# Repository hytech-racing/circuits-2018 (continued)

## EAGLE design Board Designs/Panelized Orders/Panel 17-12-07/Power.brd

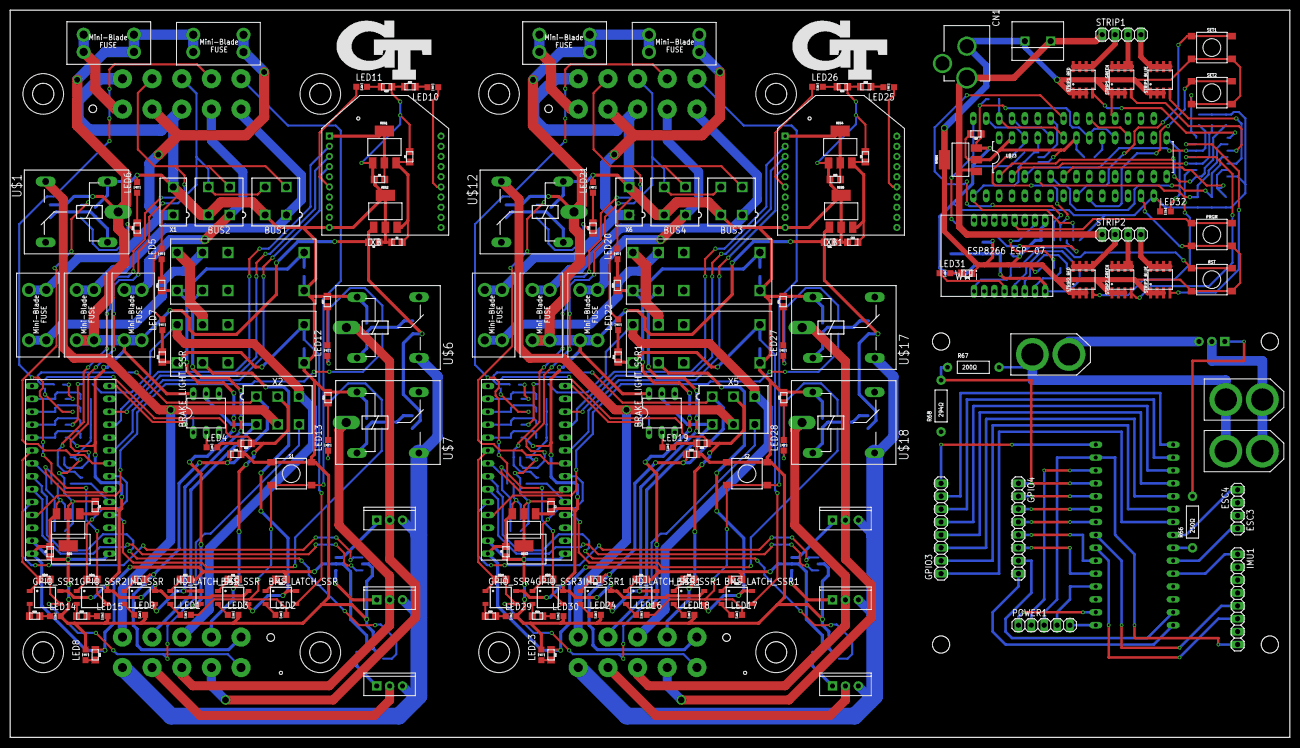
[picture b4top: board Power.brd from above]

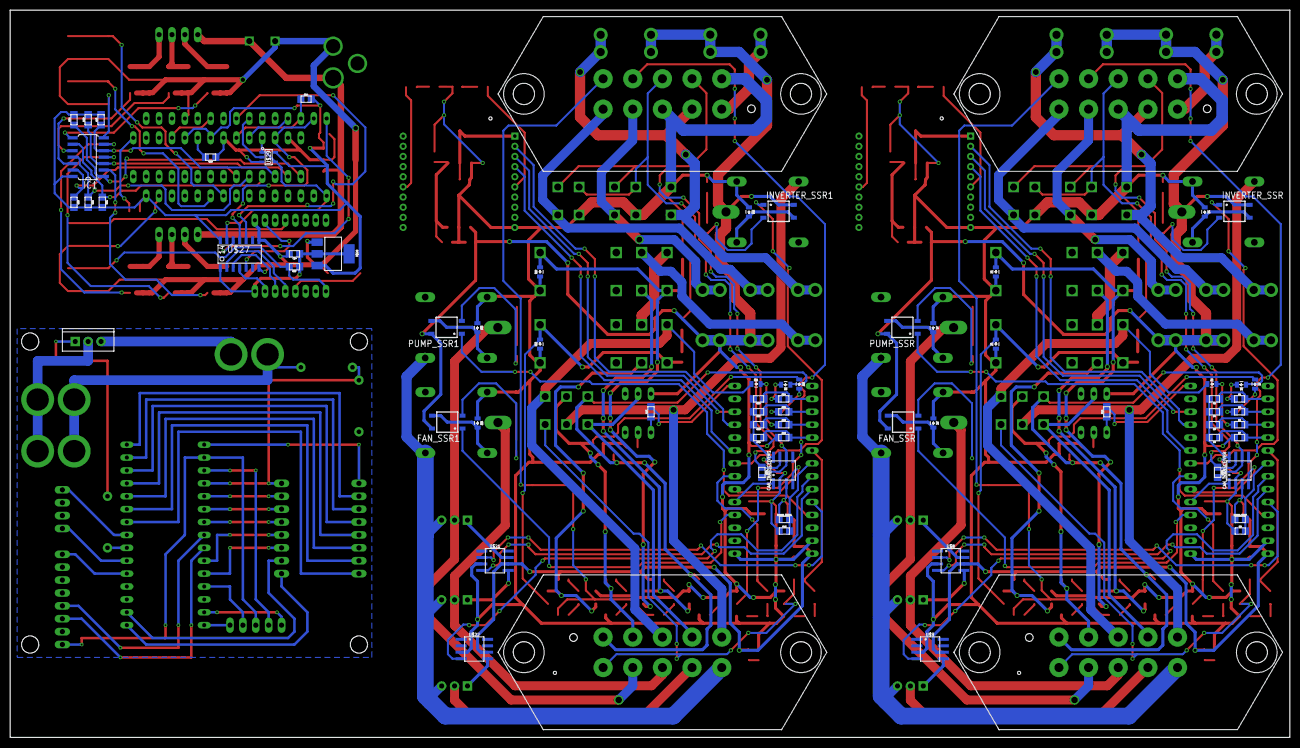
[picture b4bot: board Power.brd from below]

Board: 2 copper layers, 252.1 x 143.3 mm, 244 parts (71 on the bottom side), 240 nets.

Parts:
5VREG: SOT223
BATTERY_POWER1: XT60
BMS_LATCH_SSR, BMS_LATCH_SSR1: CPC1002N; SOP04
BMS_SSR, BMS_SSR1: CPC1002N; SOP04
BOARD_TEMP, BOARD_TEMP1: THERMISTOR_NCP210805; 0805
BRAKE_LIGHT_SSR, BRAKE_LIGHT_SSR1: SOLID_STATE_RELAY_VO14642AT; DIL06
BUS1, BUS2, BUS3, BUS4: CONNECTOR-4; MINIFIT_5566-4
C1, C5, C7, C11: .22uF; 0805
C2, C6, C8, C12: .1uF; 0805
C3, C4, C9, C10: 1uF; 0805
C13: .1µF; 0805
C14: 1µF; 0805
CAN_TRANSCEIVER, CAN_TRANSCEIVER1: MCP2551; SOIC-08
CN1: DCJACK_2MM_PTH
D1, D2, D3, D4, D5, D6, D7, D8, D9, D10, D11, D12, D13, D14, D15, D16: DIODE0805; 0805_D
ESC1_POWER1, ESC2_POWER1: XT60
ESC3, ESC4: M02; 1X02
FAN_SSR, FAN_SSR1: CPC1002N; SOP04
FH_FUSE, FH_FUSE1: 8A; MINI-BLADE_FUSE_HOLDER
FSAE_FUSE, FSAE_FUSE1: 8A; MINI-BLADE_FUSE_HOLDER
FUSE_BUS_1, FUSE_BUS_2, FUSE_BUS_3, FUSE_BUS_4: 5A; MINI-BLADE_FUSE_HOLDER
GPIO3, GPIO4: 1X08
GPIO_SSR1, GPIO_SSR2, GPIO_SSR3, GPIO_SSR4: CPC1002N; SOP04
IC1: 74HC04D; SO14
IMD_LATCH_SSR, IMD_LATCH_SSR1: CPC1002N; SOP04
IMD_SHUTDOWN, IMD_SHUTDOWN1, IMD_SHUTDOWN2, IMD_SHUTDOWN3: G2RL-2-DC12; G2RL-2
IMD_SSR, IMD_SSR1: CPC1002N; SOP04
IMU1: 1X08
INVERTER_SSR, INVERTER_SSR1: CPC1002N; SOP04
LED1, LED2, LED16, LED17: White; LED-805
LED3, LED7, LED11, LED18, LED22, LED26: Green; LED-805
LED4, LED6, LED10, LED12, LED13, LED14, LED15, LED19, LED21, LED25, LED27, LED28, LED29, LED30, LED31: Red; LED-805
LED5, LED9, LED20, LED24: Yellow; LED-805
LED8, LED23: Purple; LED-805
LED32: LED-805
POWER1: 1X05
POWER_MOSFET1: TO-220-SINK
PRGM: TACTILE_SWITCH_SMD_6.2MM_TALL
PUMP_SSR, PUMP_SSR1: CPC1002N; SOP04
R1, R3, R5, R7, R24, R36, R38, R40: 43k; 0805
R2, R4, R6, R8, R35, R37, R39, R41: 12k; 0805
R9, R19, R42, R45, R56, R57, R58, R59, R60, R61, R62, R63: 10k; 0805
R10, R11, R16, R25, R26, R29, R30, R43, R53, R54: 43; 0805
R12, R13, R23, R27, R28, R31, R32, R50, R51, R52: 33; 0805
R14, R17, R21, R33, R44, R48: 820; 0805
R15, R34: 120; 0805
R18, R46, R55: 2.2k; 0805
R20, R47: 270; 0805
R22, R49, R64: 100; 0805
R66: 250Ω; AXIAL-0.4
R67: 200Ω; AXIAL-0.4
R68: 294Ω; AXIAL-0.4
REG, REG2, REG3, REG5: 5V; SOT223
REG1, REG4: TLV1117LV33; SOT223
RST: TACTILE_SWITCH_SMD_6.2MM_TALL
S1, S2: TACTILE_SWITCH_SMD_6.2MM_TALL
SET1, SET2: TACTILE_SWITCH_SMD_6.2MM_TALL
SHUTDWN_FUSE, SHUTDWN_FUSE1: 5A; MINI-BLADE_FUSE_HOLDER
STRIP1, STRIP2: 1X04
STRIP1_BLUE, STRIP1_GREEN, STRIP1_RED, STRIP2_BLUE, STRIP2_GREEN, STRIP2_RED: MDS1656; SOIC-08
U$1, U$6, U$7, U$12, U$17, U$18: G5LE; ZF112
U$2, U$4, U$5, U$14, U$15, U$16: N-CHANNEL_MOSFETGENERIC; TO-220-SINK
U$3, U$13: TEENSY_3.2_SIMPLE
U$8, U$9, U$21, U$22: MC34152; SOIC-08
U$10, U$11, U$19, U$20: JUMPER; 0805
U$23: TLC5940; DIL28-3
U$24, U$31: ARDUINO_NANO
U$25: TERMINAL_BLOCK_DG301-02P; DG301-02P
U$26: ESP8266_ESP-07
U$27: SOIC-14
U$28: TLV1117LV33; SOT223
U$29: SN74LVC1G08; SOT-23-5
X1, X6: CONNECTOR-2; MINIFIT_5566-2
X2, X5: CONNECTOR-6; MINIFIT_5566-6
X3, X4, X7, X8: CONNECTOR-10MX150L_VERTICAL-10; MX150L_VERTICAL-10
XB, XB1: XBEE

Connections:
3.3V1: IMU1.8, POWER1.3, U$31.3.3V
5V1: POWER1.4, U$31.5V
12VSUPPLY_BRB: FH_FUSE.R1, FH_FUSE.R2, SHUTDWN_FUSE.R1, SHUTDWN_FUSE.R2, X1.1, X4.2
12VSUPPLY_BRB1: FH_FUSE1.R1, FH_FUSE1.R2, SHUTDWN_FUSE1.R1, SHUTDWN_FUSE1.R2, X6.1, X8.2
12VSUPPLY_FSAE: FSAE_FUSE.R1, FSAE_FUSE.R2, X4.1
12VSUPPLY_FSAE1: FSAE_FUSE1.R1, FSAE_FUSE1.R2, X8.1
12VSUPPLY_READ: R7.2, R8.1, U$3.A3
12VSUPPLY_READ1: R40.2, R41.1, U$13.A3
12V_F1: BUS1.1, FUSE_BUS_1.R1, FUSE_BUS_1.R2, X4.5
12V_F2: BUS2.1, FUSE_BUS_2.R1, FUSE_BUS_2.R2, X4.4
12V_F3: BUS3.1, FUSE_BUS_3.R1, FUSE_BUS_3.R2, X8.5
12V_F4: BUS4.1, FUSE_BUS_4.R1, FUSE_BUS_4.R2, X8.4
+3V3: C14.1, R57.1, U$26.P$8, U$27.1, U$28.2, U$28.4
+5V: BOARD_TEMP.1, C2.2, CAN_TRANSCEIVER.3, R12.2, R13.1, R20.1, REG.3, U$3.VIN, U$8.6, U$9.6
+5V1: BOARD_TEMP1.1, C8.2, CAN_TRANSCEIVER1.3, R31.2, R32.1, R47.1, REG3.3, U$13.VIN, U$21.6, U$22.6
+5V2: 5VREG.3, C13.1, IC1.14, LED32.A, R56.2, R58.2, R59.2, R60.2, R61.2, R62.2, R63.2, U$23.19, U$23.21, U$24.VIN, U$27.14, U$28.3, U$29.5
+12V: BMS_SSR.4, BRAKE_LIGHT_SSR.6, C1.2, C5.2, FAN_SSR.4, FH_FUSE.L1, FH_FUSE.L2, FSAE_FUSE.L1, FSAE_FUSE.L2, FUSE_BUS_1.L1, FUSE_BUS_1.L2, FUSE_BUS_2.L1, FUSE_BUS_2.L2, GPIO_SSR1.4, GPIO_SSR2.4, IMD_SSR.4, INVERTER_SSR.4, PUMP_SSR.4, R7.1, REG.1, REG2.1, U$1.P
+12V1: BMS_SSR1.4, BRAKE_LIGHT_SSR1.6, C7.2, C11.2, FAN_SSR1.4, FH_FUSE1.L1, FH_FUSE1.L2, FSAE_FUSE1.L1, FSAE_FUSE1.L2, FUSE_BUS_3.L1, FUSE_BUS_3.L2, FUSE_BUS_4.L1, FUSE_BUS_4.L2, GPIO_SSR3.4, GPIO_SSR4.4, IMD_SSR1.4, INVERTER_SSR1.4, PUMP_SSR1.4, R40.1, REG3.1, REG5.1, U$12.P
+12V2: 5VREG.1, CN1.PWR, STRIP1.1, STRIP2.1, U$25.1
A4: GPIO4.1, R67.P$1, R68.P$2, U$31.A0
A5: GPIO4.2, U$31.A1
A8: GPIO4.3, U$31.A2
A9: GPIO4.4, U$31.A3
A10: GPIO4.5, U$31.A6
A11: GPIO4.6, U$31.A7
AREF1: POWER1.2, U$31.AREF
BLANK: R56.1, U$23.23, U$24.D10
BMS_COIL_PWR: BMS_LATCH_SSR.3, D5.C, IMD_SHUTDOWN1.4, IMD_SHUTDOWN1.COIL-, R17.1
BMS_COIL_PWR1: BMS_LATCH_SSR1.3, D13.C, IMD_SHUTDOWN3.4, IMD_SHUTDOWN3.COIL-, R44.1
BMS_OK: D2.A, R11.2, R19.1, X2.2, X3.2
BMS_OK1: D10.A, R26.2, R45.1, X5.2, X7.2
BMS_OK_READ: R3.2, R4.1, U$3.A1
BMS_OK_READ1: R36.2, R37.1, U$13.A1
BMS_PWR_STEP: BMS_LATCH_SSR.4, BMS_SSR.3, IMD_SHUTDOWN1.3
BMS_PWR_STEP1: BMS_LATCH_SSR1.4, BMS_SSR1.3, IMD_SHUTDOWN3.3
BRAKE_LIGHT: BRAKE_LIGHT_SSR.5, X2.4, X3.4
BRAKE_LIGHT1: BRAKE_LIGHT_SSR1.5, X5.4, X7.4
BRAKE_LIGHT_CTRL: R10.2, U$3.D12
BRAKE_LIGHT_CTRL1: R25.2, U$13.D12
CANH: BUS1.4, BUS2.4, CAN_TRANSCEIVER.7, R15.1, X4.8
CANH1: BUS3.4, BUS4.4, CAN_TRANSCEIVER1.7, R34.1, X8.8
CANL: BUS1.3, BUS2.3, CAN_TRANSCEIVER.6, R15.2, X4.7
CANL1: BUS3.3, BUS4.3, CAN_TRANSCEIVER1.6, R34.2, X8.7
D0(RX)1: GPIO4.7, U$31.D0(RX)
D1: GPIO3.8, U$31.D13
D1(TX)1: GPIO4.8, U$31.D1(TX)
D2: GPIO3.7, U$31.D12
D3: GPIO3.6, U$31.D11
D4: GPIO3.5, U$31.D10
D5: GPIO3.4, U$31.D9
D14: GPIO3.3, U$31.D8
D15: GPIO3.2, U$31.D7
D16: GPIO3.1, U$31.D6
DRIVE1: R66.P$1, U$31.D4
ESC3: ESC3.2, U$31.D3
ESC4: ESC4.2, U$31.D5
FAN1-: U$4.2, U$7.P, X3.8
FAN1-1: U$15.2, U$18.P, X7.8
FAN2-: U$5.2, X3.9
FAN2-1: U$16.2, X7.9
GND: BUS1.2, BUS2.2, C1.1, C2.1, C3.2, C4.1, C5.1, C6.1, CAN_TRANSCEIVER.2, CAN_TRANSCEIVER.8, D4.A, D5.A, D6.A, D7.A, D8.A, IMD_SHUTDOWN.COIL+, IMD_SHUTDOWN1.COIL+, LED3.C, LED4.C, LED5.C, LED6.C, LED7.C, LED8.C, LED9.C, LED14.C, LED15.C, R2.2, R4.2, R6.2, R8.2, R9.1, R18.2, R19.2, R22.1, R23.1, R27.2, R28.2, REG.2, REG.4, REG1.1, REG2.2, REG2.4, S1.B1, S1.B2, U$1.2, U$3.AGND, U$3.GND, U$6.1, U$7.1, U$8.3, U$9.3, X1.2, X4.3, X4.6, XB.10
GND1: U$2.3, U$4.3, U$5.3, U$6.S, U$7.S, X3.10
GND2: BUS3.2, BUS4.2, C7.1, C8.1, C9.2, C10.1, C11.1, C12.1, CAN_TRANSCEIVER1.2, CAN_TRANSCEIVER1.8, D12.A, D13.A, D14.A, D15.A, D16.A, IMD_SHUTDOWN2.COIL+, IMD_SHUTDOWN3.COIL+, LED18.C, LED19.C, LED20.C, LED21.C, LED22.C, LED23.C, LED24.C, LED29.C, LED30.C, R35.2, R37.2, R39.2, R41.2, R42.1, R45.2, R46.2, R49.1, R50.1, R51.2, R52.2, REG3.2, REG3.4, REG4.1, REG5.2, REG5.4, S2.B1, S2.B2, U$12.2, U$13.AGND, U$13.GND, U$17.1, U$18.1, U$21.3, U$22.3, X6.2, X8.3, X8.6, XB1.10
GND3: U$14.3, U$15.3, U$16.3, U$17.S, U$18.S, X7.10
GND4: 5VREG.2, 5VREG.4, C13.2, C14.2, CN1.GND, IC1.7, PRGM.A1, PRGM.A2, R55.1, R64.1, RST.A1, RST.A2, SET1.A1, SET1.A2, SET2.A1, SET2.A2, STRIP1_BLUE.1, STRIP1_BLUE.2, STRIP1_BLUE.3, STRIP1_GREEN.1, STRIP1_GREEN.2, STRIP1_GREEN.3, STRIP1_RED.1, STRIP1_RED.2, STRIP1_RED.3, STRIP2_BLUE.1, STRIP2_BLUE.2, STRIP2_BLUE.3, STRIP2_GREEN.1, STRIP2_GREEN.2, STRIP2_GREEN.3, STRIP2_RED.1, STRIP2_RED.2, STRIP2_RED.3, U$23.22, U$23.27, U$24.GND, U$24.GND1, U$25.2, U$26.P$9, U$27.7, U$27.8, U$28.1, U$29.3
GND6: BATTERY_POWER1.-, ESC3.1, ESC4.1, IMU1.7, POWER1.1, POWER_MOSFET1.3, R68.P$1, U$31.GND, U$31.GND1
GPIO_1: GPIO_SSR1.3, U$10.2, X2.6, X3.6
GPIO_2: GPIO_SSR2.3, U$11.2, X4.9
GPIO_3: GPIO_SSR3.3, U$20.2, X8.9
GPIO_4: GPIO_SSR4.3, U$19.2, X5.6, X7.6
GPIO_CTRL1: GPIO_SSR1.1, U$3.A4, U$10.1
GPIO_CTRL2: GPIO_SSR2.1, U$3.D5, U$11.1
GPIO_CTRL4: GPIO_SSR3.1, U$13.D5, U$20.1
GPIO_CTRL6: GPIO_SSR4.1, U$13.A4, U$19.1
IMD_COIL_PWR: D6.C, IMD_LATCH_SSR.3, IMD_SHUTDOWN.4, IMD_SHUTDOWN.COIL-, R14.1
IMD_COIL_PWR1: D14.C, IMD_LATCH_SSR1.3, IMD_SHUTDOWN2.4, IMD_SHUTDOWN2.COIL-, R33.1
IMD_PWR_STEP: IMD_LATCH_SSR.4, IMD_SHUTDOWN.3, IMD_SSR.3
IMD_PWR_STEP1: IMD_LATCH_SSR1.4, IMD_SHUTDOWN2.3, IMD_SSR1.3
INT1: IMU1.1, U$31.D2
INVERTER_CTRL: INVERTER_SSR.1, U$3.D6
INVERTER_CTRL1: INVERTER_SSR1.1, U$13.D6
INVERTER_SUPPLY: U$1.S, X2.5, X3.5
INVERTER_SUPPLY1: U$12.S, X5.5, X7.5
LATCH_EXT_BUTTON: LED1.C, LED2.C, S1.A1, S1.A2, X4.10
LATCH_EXT_BUTTON1: LED16.C, LED17.C, S2.A1, S2.A2, X8.10
MISO: U$24.D12, U$27.12
MISO_33: U$26.P$6, U$27.3
MOSI: U$23.26, U$24.D11, U$27.11
MOSI_33: U$26.P$7, U$27.4
unnamed: IMD_LATCH_SSR.2, LED1.A
unnamed: CAN_TRANSCEIVER.4, U$3.D4(CANRX)
unnamed: CAN_TRANSCEIVER.1, U$3.D3(CANTX)
unnamed: D7.C, PUMP_SSR.3, U$6.2
unnamed: IMD_LATCH_SSR.1, R12.1
unnamed: GPIO_SSR1.2, R29.1
unnamed: BRAKE_LIGHT_SSR.2, LED4.A
unnamed: GPIO_SSR2.2, R30.1
unnamed: BMS_SSR.2, LED3.A
unnamed: LED10.A, XB.15
unnamed: LED10.C, R22.2
unnamed: BMS_LATCH_SSR.1, R13.2
unnamed: LED14.A, R29.2
unnamed: LED15.A, R30.2
unnamed: BOARD_TEMP.2, R9.2, U$3.A5
unnamed: BMS_LATCH_SSR.2, LED2.A
unnamed: BRAKE_LIGHT_SSR.1, R10.1
unnamed: BMS_SSR.1, R11.1
unnamed: LED5.A, R14.2
unnamed: D8.C, FAN_SSR.3, U$7.2
unnamed: CAN_TRANSCEIVER1.4, U$13.D4(CANRX)
unnamed: D1.C, R1.1
unnamed: D2.C, R3.1
unnamed: D3.C, R5.1
unnamed: LED11.A, XB.6
unnamed: D4.C, INVERTER_SSR.3, U$1.1
unnamed: INVERTER_SSR.2, R16.1
unnamed: LED6.A, R16.2
unnamed: LED8.A, R20.2
unnamed: CAN_TRANSCEIVER1.1, U$13.D3(CANTX)
unnamed: IMD_SSR.1, R21.2
unnamed: LED7.A, R17.2
unnamed: LED11.C, R23.2
unnamed: IMD_SSR.2, LED9.A
unnamed: C3.1, C6.2, REG1.3, REG2.3
unnamed: LED13.C, R28.1
unnamed: LED12.C, R27.1
unnamed: LED12.A, PUMP_SSR.2
unnamed: U$2.1, U$8.7
unnamed: U$4.1, U$8.5
unnamed: U$5.1, U$9.5
unnamed: FAN_SSR.2, LED13.A
unnamed: BOARD_TEMP1.2, R42.2, U$13.A5
unnamed: IMD_LATCH_SSR1.2, LED16.A
unnamed: BMS_SSR1.2, LED18.A
unnamed: BMS_SSR1.1, R26.1
unnamed: BRAKE_LIGHT_SSR1.2, LED19.A
unnamed: BRAKE_LIGHT_SSR1.1, R25.1
unnamed: LED20.A, R33.2
unnamed: D9.C, R24.1
unnamed: D10.C, R36.1
unnamed: D11.C, R38.1
unnamed: D12.C, INVERTER_SSR1.3, U$12.1
unnamed: INVERTER_SSR1.2, R43.1
unnamed: LED21.A, R43.2
unnamed: IMD_LATCH_SSR1.1, R31.1
unnamed: BMS_LATCH_SSR1.2, LED17.A
unnamed: BMS_LATCH_SSR1.1, R32.2
unnamed: LED22.A, R44.2
unnamed: LED23.A, R47.2
unnamed: IMD_SSR1.2, LED24.A
unnamed: IMD_SSR1.1, R48.2
unnamed: LED25.A, XB1.15
unnamed: LED25.C, R49.2
unnamed: LED26.C, R50.2
unnamed: LED26.A, XB1.6
unnamed: C9.1, C12.2, REG4.3, REG5.3
unnamed: U$14.1, U$21.7
unnamed: U$15.1, U$21.5
unnamed: U$16.1, U$22.5
unnamed: D15.C, PUMP_SSR1.3, U$17.2
unnamed: D16.C, FAN_SSR1.3, U$18.2
unnamed: LED28.C, R52.1
unnamed: LED27.C, R51.1
unnamed: LED27.A, PUMP_SSR1.2
unnamed: FAN_SSR1.2, LED28.A
unnamed: GPIO_SSR4.2, R53.1
unnamed: GPIO_SSR3.2, R54.1
unnamed: LED29.A, R53.2
unnamed: LED30.A, R54.2
unnamed: R55.2, U$23.20
unnamed: U$23.18, U$24.D3
unnamed: STRIP2.2, STRIP2_RED.5, STRIP2_RED.6, STRIP2_RED.7, STRIP2_RED.8
unnamed: STRIP1.2, STRIP1_RED.5, STRIP1_RED.6, STRIP1_RED.7, STRIP1_RED.8
unnamed: STRIP1.3, STRIP1_GREEN.5, STRIP1_GREEN.6, STRIP1_GREEN.7, STRIP1_GREEN.8
unnamed: STRIP1.4, STRIP1_BLUE.5, STRIP1_BLUE.6, STRIP1_BLUE.7, STRIP1_BLUE.8
unnamed: STRIP2.3, STRIP2_GREEN.5, STRIP2_GREEN.6, STRIP2_GREEN.7, STRIP2_GREEN.8
unnamed: STRIP2.4, STRIP2_BLUE.5, STRIP2_BLUE.6, STRIP2_BLUE.7, STRIP2_BLUE.8
unnamed: R57.2, RST.B1, RST.B2, U$26.P$1
unnamed: IC1.2, STRIP2_RED.4
unnamed: IC1.4, STRIP2_GREEN.4
unnamed: IC1.8, STRIP1_RED.4
unnamed: IC1.10, STRIP1_GREEN.4
unnamed: IC1.12, STRIP1_BLUE.4
unnamed: IC1.6, STRIP2_BLUE.4
unnamed: IC1.1, R58.1, U$23.1
unnamed: IC1.3, R59.1, U$23.2
unnamed: IC1.5, R60.1, U$23.3
unnamed: IC1.13, R63.1, U$23.6
unnamed: IC1.11, R62.1, U$23.5
unnamed: IC1.9, R61.1, U$23.4
unnamed: PRGM.B1, PRGM.B2, U$26.P$12
unnamed: LED31.A, U$26.P$4
unnamed: LED32.C, U$23.15
unnamed: LED31.C, R64.2
unnamed: POWER_MOSFET1.1, R66.P$2
OKHS: D1.A, R18.1, R21.1, X2.1, X3.1
OKHS1: D9.A, R46.1, R48.1, X5.1, X7.1
OKHS_READ: R1.2, R2.1, U$3.A0
OKHS_READ1: R24.2, R35.1, U$13.A0
PUMP1-: U$2.2, U$6.P, X3.7
PUMP1-1: U$14.2, U$17.P, X7.7
PWM_CTRL1: U$3.A8, U$8.2
PWM_CTRL2: U$3.A7, U$8.4
PWM_CTRL3: U$3.A6, U$9.4
PWM_CTRL4: U$13.A6, U$22.4
PWM_CTRL5: U$13.A7, U$21.4
PWM_CTRL6: U$13.A8, U$21.2
RELAY_CTRL1: PUMP_SSR.1, U$3.A9
RELAY_CTRL2: FAN_SSR.1, U$3.D2
RELAY_CTRL3: FAN_SSR1.1, U$13.D2
RELAY_CTRL4: PUMP_SSR1.1, U$13.A9
SCK: U$23.25, U$24.D13, U$27.13, U$29.1, U$29.4
SCK_33: U$26.P$5, U$27.2
SCL1: IMU1.6, U$31.A5
SDA1: IMU1.5, U$31.A4
SET1: SET1.B1, SET1.B2, U$24.A5
SET2: SET2.B1, SET2.B2, U$24.A6
SHUTDOWN_A: IMD_SHUTDOWN.6, SHUTDWN_FUSE.L1, SHUTDWN_FUSE.L2
SHUTDOWN_A1: IMD_SHUTDOWN2.6, SHUTDWN_FUSE1.L1, SHUTDWN_FUSE1.L2
SHUTDOWN_B: IMD_SHUTDOWN.5, IMD_SHUTDOWN1.6
SHUTDOWN_B1: IMD_SHUTDOWN2.5, IMD_SHUTDOWN3.6
SHUTDOWN_C: D3.A, IMD_SHUTDOWN1.5, X2.3, X3.3
SHUTDOWN_C1: D11.A, IMD_SHUTDOWN3.5, X5.3, X7.3
SHUTDOWN_OUT_READ: R5.2, R6.1, U$3.A2
SHUTDOWN_OUT_READ1: R38.2, R39.1, U$13.A2
SS_ESP8266: U$24.D5, U$27.10
SS_ESP8266_33: U$26.P$10, U$27.5
SS_TLC5940: U$24.D6, U$29.2
SUPPLY+1: BATTERY_POWER1.+, ESC1_POWER1.+, ESC2_POWER1.+, R67.P$2
SUPPLY-1: ESC1_POWER1.-, ESC2_POWER1.-, POWER_MOSFET1.2
VCC: C4.2, REG1.2, REG1.4, XB.1
VCC1: C10.2, REG4.2, REG4.4, XB1.1
VIN1: POWER1.5, U$31.VIN
XB1: U$13.D7(RX3), XB1.4
XB8: U$3.D7(RX3), XB.4
XBDI: U$3.D10(TX2), XB.3
XBDI1: U$13.D10(TX2), XB1.3
XBDO: U$3.D9(RX2), XB.2
XBDO1: U$13.D9(RX2), XB1.2
XLAT: U$23.24, U$24.D9

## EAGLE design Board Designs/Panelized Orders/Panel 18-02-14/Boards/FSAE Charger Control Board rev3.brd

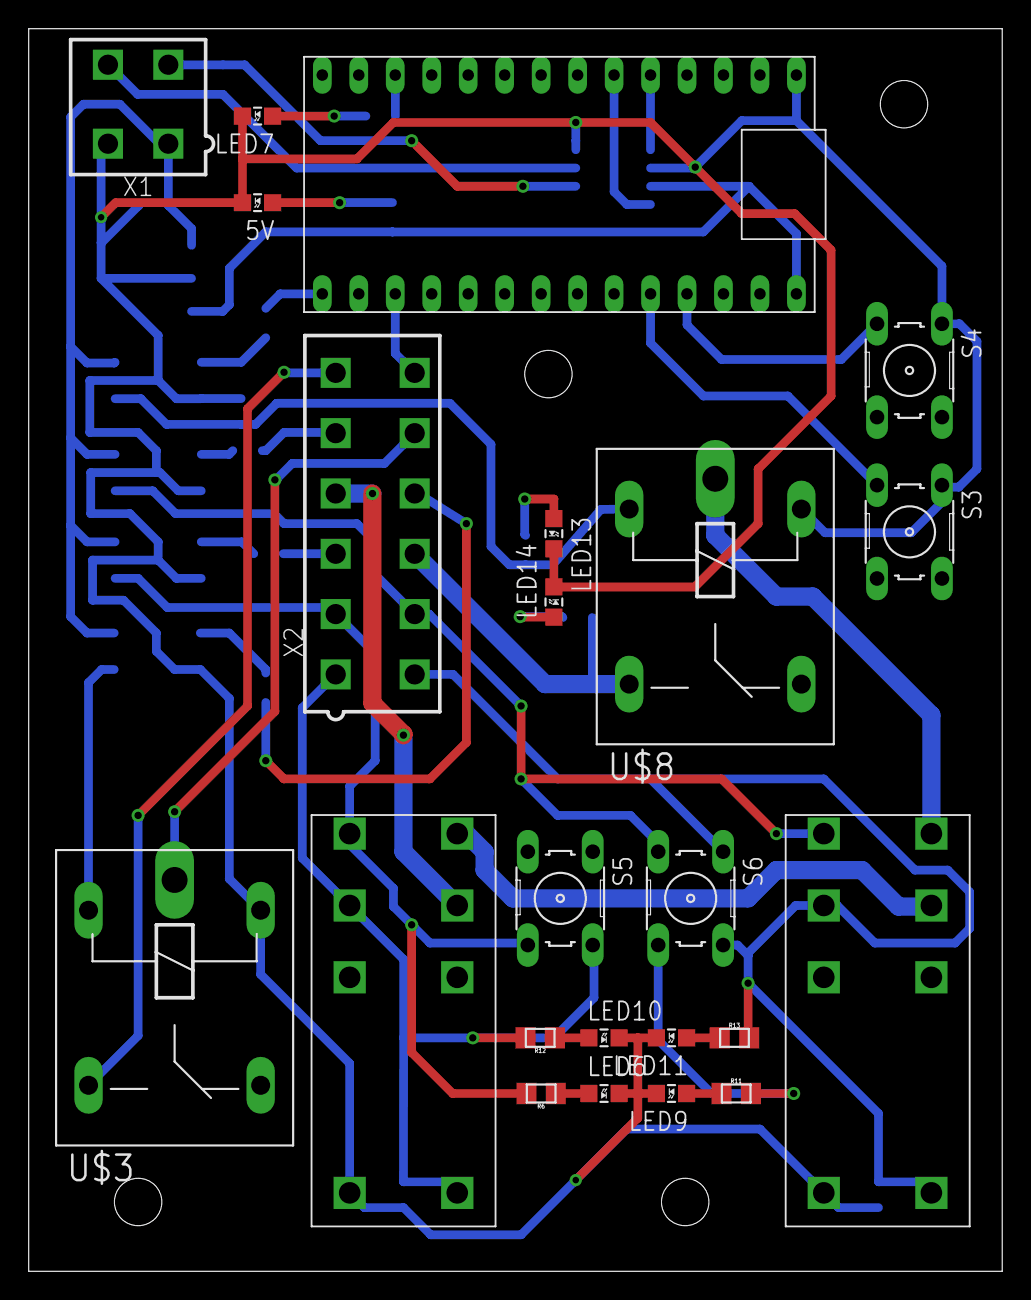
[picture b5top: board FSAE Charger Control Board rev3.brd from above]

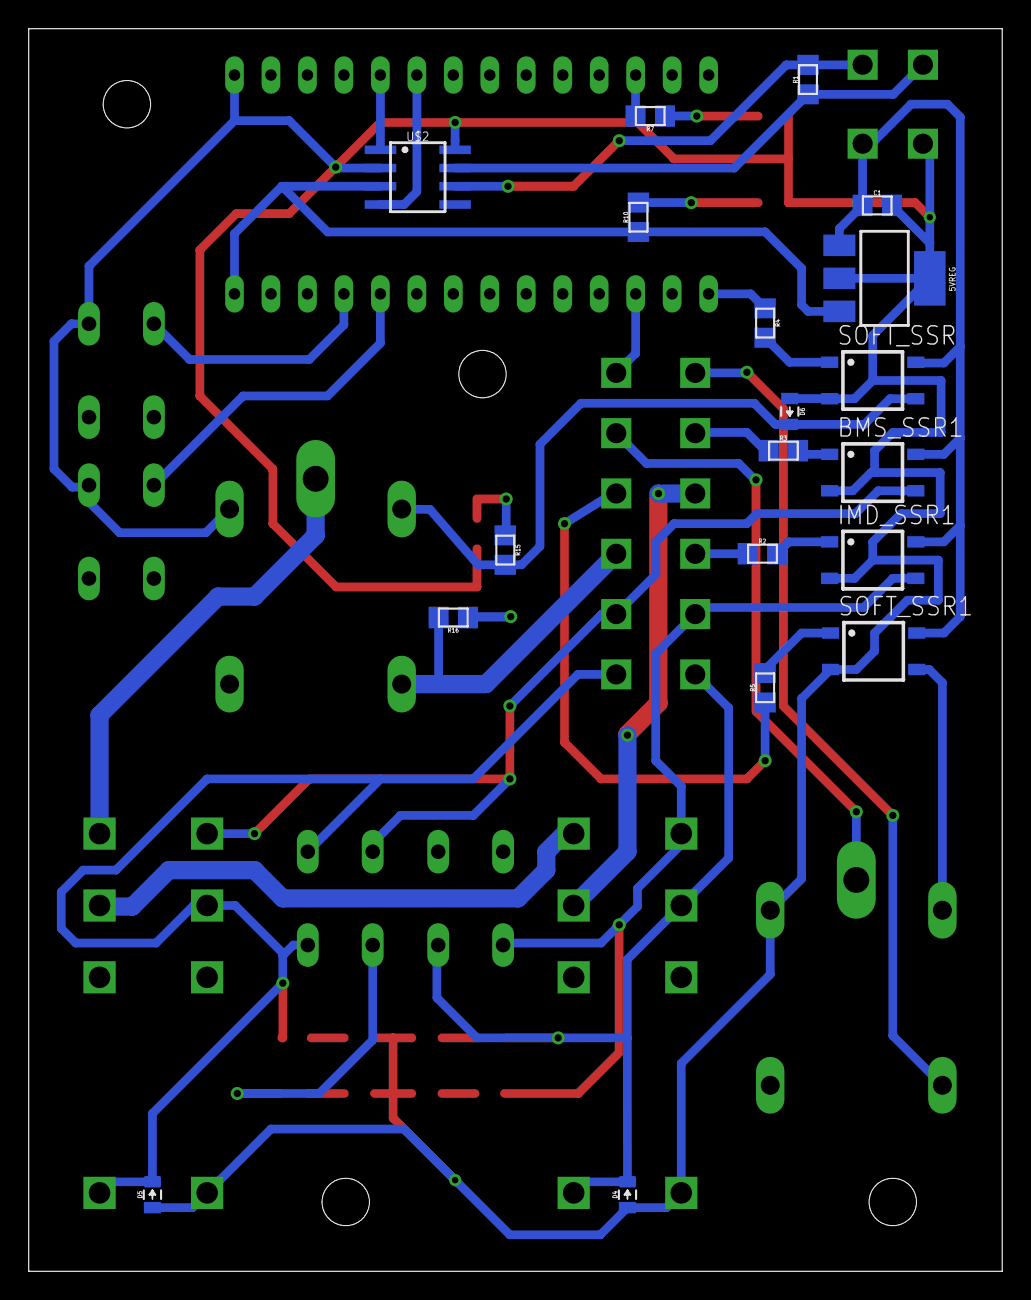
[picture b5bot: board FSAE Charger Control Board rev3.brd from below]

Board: 2 copper layers, 67.8 x 86.5 mm, 42 parts (19 on the bottom side), 39 nets.

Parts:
5V: LED-805
5VREG: SOT223
BMS_SSR1: CPC1002N; SOP04
C1: .22uF; 0805
D4, D5, D6: DIODE0805; 0805_D
IMD_SSR1: CPC1002N; SOP04
LED6, LED7, LED9, LED10, LED11, LED13, LED14: LED-805
R1: 120; 0805
R2, R3, R4, R5, R6, R7, R10, R11, R12, R13, R15, R16: 0805
S3, S4, S5, S6: B3F-10XX
SOFT_SSR, SOFT_SSR1: CPC1002N; SOP04
U$1: TEENSY_3.2_SIMPLE
U$2: MCP2551; SOIC-08
U$3, U$8: G5LE; ZF112
U$6, U$7: G2RL-2-DC12; G2RL-2
X1: CONNECTOR-4; MINIFIT_5566-4
X2: CONNECTOR-12; MINIFIT_5566-12

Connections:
+5V: 5VREG.3, R10.1, U$1.VIN, U$2.3
+12V: 5VREG.1, BMS_SSR1.4, C1.1, IMD_SSR1.4, SOFT_SSR.4, SOFT_SSR1.4, X1.1
BMS_12V: BMS_SSR1.3, R11.2, S6.3, S6.4, U$7.4, X2.8
BMS_INRLK: R5.1, X2.10
BMS_OK: D5.C, R13.2, S6.1, S6.2, U$7.3, U$7.COIL-, X2.7
BTN_X: S4.3, U$1.A9
BTN_Y: S3.3, U$1.A8
CANH: R1.1, U$2.7, X1.4
CANL: R1.2, U$2.6, X1.3
CANRX: U$1.D4(CANRX), U$2.4
CANTX: U$1.D3(CANTX), U$2.1
GND: 5V.C, 5VREG.2, 5VREG.4, BMS_SSR1.2, C1.2, D4.A, D5.A, D6.A, IMD_SSR1.2, LED6.C, LED7.C, LED9.C, LED10.C, LED11.C, LED13.C, LED14.C, S3.1, S4.1, SOFT_SSR.2, SOFT_SSR1.2, U$1.GND, U$2.2, U$2.8, U$3.1, U$6.COIL+, U$7.COIL+, U$8.1, X1.2
GPIO: U$1.A1, X2.12
IMD_12V: IMD_SSR1.3, R6.2, S5.3, S5.4, U$6.4, X2.2
IMD_OK: D4.C, R12.2, S5.1, S5.2, U$6.3, U$6.COIL-, X2.1
unnamed: SOFT_SSR1.3, U$3.2
unnamed: LED7.A, R7.1
unnamed: 5V.A, R10.2
unnamed: IMD_SSR1.1, R2.2
unnamed: U$3.S, X2.6
unnamed: LED6.A, R6.1
unnamed: LED9.A, R11.1
unnamed: LED10.A, R12.1
unnamed: U$3.P, X2.11
unnamed: R7.2, U$1.D10(TX2)
unnamed: BMS_SSR1.1, R3.2
unnamed: LED11.A, R13.1
unnamed: LED14.A, R16.1
unnamed: LED13.A, R15.1
unnamed: R2.1, X2.3
unnamed: R3.1, X2.5
unnamed: R5.2, SOFT_SSR1.1
unnamed: R4.1, U$1.D13
SHUTDOWN_IN: U$6.6, X2.4
SHUTDOWN_IN_A: U$6.5, U$7.6
SHUTDOWN_IN_B: U$7.5, U$8.P
SHUTDOWN_OUT: R16.2, U$8.S, X2.9
SW_KILL: R4.2, SOFT_SSR.1
SW_KILL_RELAY: D6.C, R15.2, SOFT_SSR.3, U$8.2

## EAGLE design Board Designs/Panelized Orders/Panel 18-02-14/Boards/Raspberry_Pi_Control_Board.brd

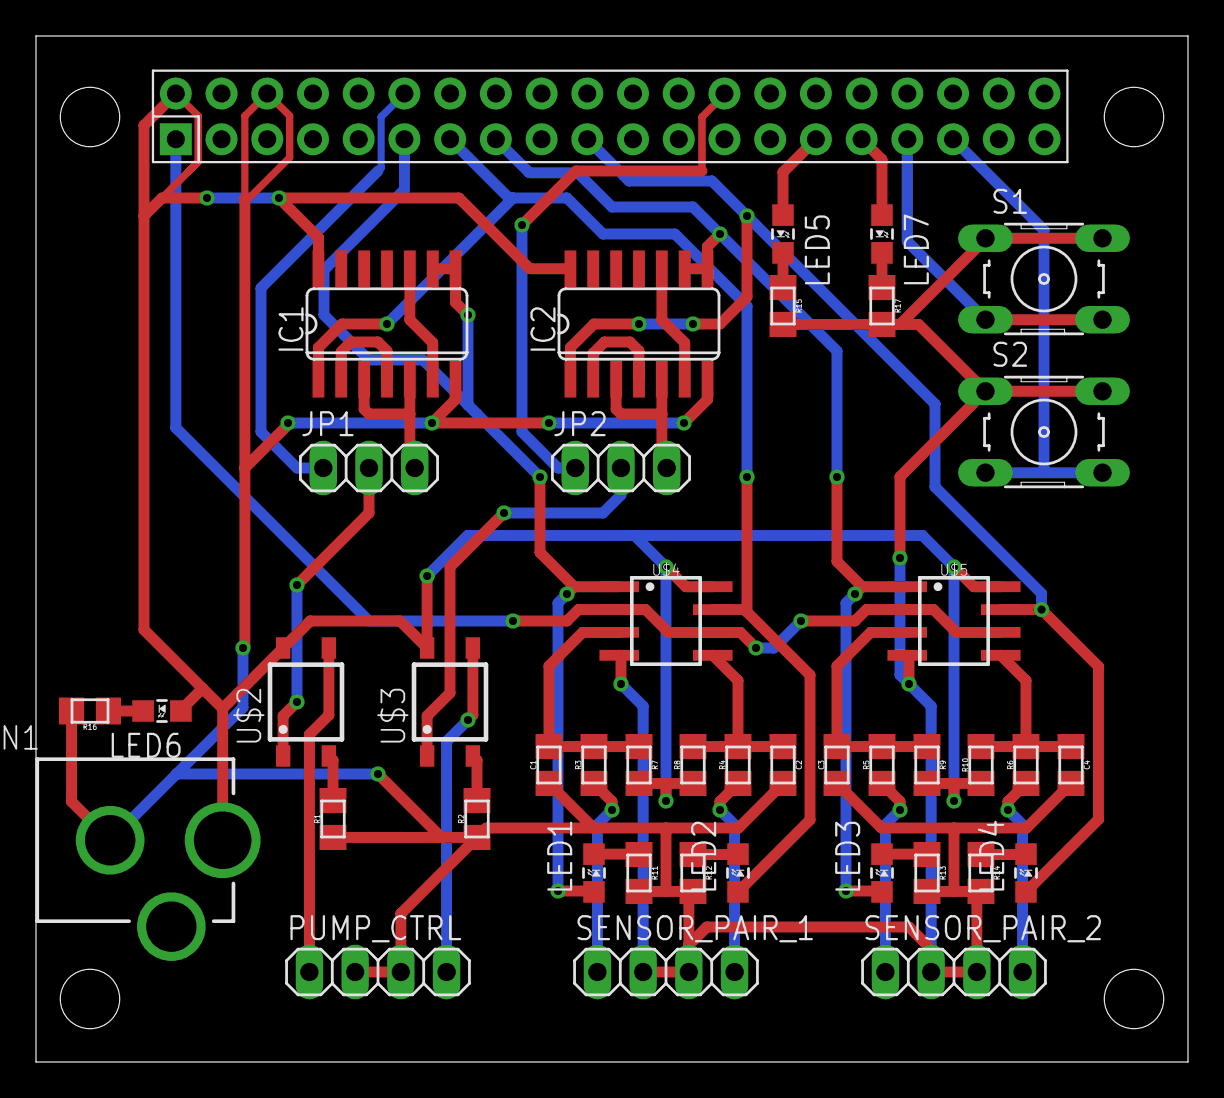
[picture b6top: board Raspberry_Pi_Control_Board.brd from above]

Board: 2 copper layers, 64.0 x 57.0 mm, 43 parts (0 on the bottom side), 40 nets.

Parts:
C1, C2, C3, C4: 1µ; 0805
CN1: DCJACK_2MM_PTH
IC1, IC2: 4001D; SO14
JP1, JP2: 1X03
LED1, LED7: RED; LED-805
LED2: BLUE; LED-805
LED3, LED5: GREEN; LED-805
LED4: ORANGE; LED-805
LED6: PURPLE; LED-805
PUMP_CTRL: 1X04
R1, R2: 270; 0805
R3, R4, R5, R6: 330; 0805
R7, R8, R9, R10: 2M; 0805
R11, R12, R13, R14: 100; 0805
R15, R16, R17: 150; 0805
S1, S2: B3F-10XX
SENSOR_PAIR_1, SENSOR_PAIR_2: 1X04
U$1: RASPBERRY_PI_HEADER
U$2, U$3: CPC1002N; SOP04
U$4, U$5: MCP6002SOIC; SOIC-08

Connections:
!Q1: IC1.2, IC1.4
!Q2: IC2.2, IC2.4
+3V3: U$1.1, U$4.2, U$4.6, U$5.2, U$5.6
+5V: CN1.PWR, IC1.14, IC2.14, LED6.A, R7.2, R8.1, R9.2, R10.1, U$1.2, U$2.4, U$3.4, U$4.8, U$5.8
BUT1: S1.3, S1.4, U$1.33
BUT2: S2.3, S2.4, U$1.35
CHARGE1: C1.2, R3.2, R7.1, U$4.3
CHARGE2: C2.1, R4.2, R8.2, U$4.5
CHARGE3: C3.2, R5.2, R9.1, U$5.3
CHARGE4: C4.1, R6.2, R10.2, U$5.5
GND: C1.1, C2.2, C3.1, C4.2, CN1.GND, IC1.7, IC2.7, PUMP_CTRL.2, PUMP_CTRL.3, R1.1, R2.1, R11.2, R12.2, R13.2, R14.2, R15.2, R16.2, R17.2, S1.1, S1.2, S2.1, S2.2, SENSOR_PAIR_1.2, SENSOR_PAIR_1.3, SENSOR_PAIR_2.2, SENSOR_PAIR_2.3, U$1.6, U$4.4, U$5.4
LED1: LED5.A, U$1.29
LED2: LED7.A, U$1.31
unnamed: R1.2, U$2.2
unnamed: R2.2, U$3.2
unnamed: PUMP_CTRL.1, U$2.3
unnamed: PUMP_CTRL.4, U$3.3
unnamed: R5.1, SENSOR_PAIR_2.1
unnamed: R6.1, SENSOR_PAIR_2.4
unnamed: R4.1, SENSOR_PAIR_1.4
unnamed: R3.1, SENSOR_PAIR_1.1
unnamed: LED1.C, R11.1
unnamed: LED2.C, R12.1
unnamed: LED3.C, R13.1
unnamed: LED4.C, R14.1
unnamed: LED5.C, R15.1
unnamed: LED6.C, R16.1
unnamed: LED7.C, R17.1
PI_PUMP_CTRL1: JP1.1, U$1.12
PI_PUMP_CTRL2: JP2.1, U$1.26
PUMP_CTRL1: JP1.2, U$2.1
PUMP_CTRL2: JP2.2, U$3.1
Q1: IC1.3, IC1.5, JP1.3
Q2: IC2.3, IC2.5, JP2.3
S1: IC1.8, IC1.9, LED1.A, U$1.11, U$4.1
S2: IC1.1, LED2.A, U$1.13, U$4.7
S3: IC2.8, IC2.9, LED3.A, U$1.15, U$5.1
S4: IC2.1, LED4.A, U$1.19, U$5.7
SET_P1_ON: IC1.6, IC1.10
SET_P2_ON: IC2.6, IC2.10

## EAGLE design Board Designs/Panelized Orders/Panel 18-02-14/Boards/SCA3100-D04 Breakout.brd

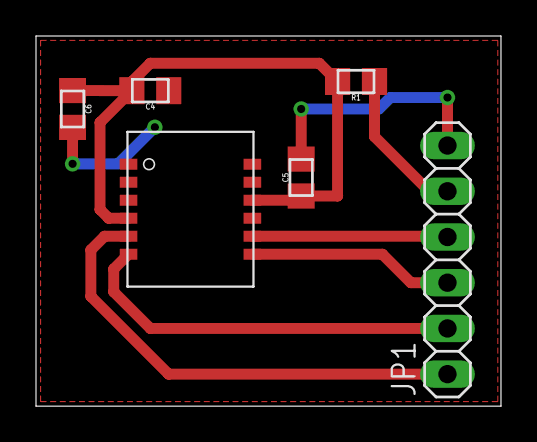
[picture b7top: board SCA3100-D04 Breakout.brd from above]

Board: 2 copper layers, 25.8 x 20.6 mm, 6 parts (0 on the bottom side), 7 nets.

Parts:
C4, C5: 100 nF; 0805
C6: 10 uF; 0805
JP1: 1X06
R1: 10 ohm; 0805
U$1: SCA3100-D04

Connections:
CSB: JP1.1, U$1.CSB
GND: C4.1, C5.2, C6.2, JP1.6, U$1.AVSS, U$1.DVSS, U$1.EGND, U$1.NC1, U$1.NC2
MISO: JP1.2, U$1.MISO
MOSI: JP1.4, U$1.MOSI
unnamed: C4.2, C5.1, C6.1, R1.2, U$1.AVDD, U$1.DVDD
SCK: JP1.3, U$1.SCK
VDD: JP1.5, R1.1
